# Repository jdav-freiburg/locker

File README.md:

# Fjaelllada - RFID controlled lockers 

> The following documentation is still work in progress, 
> for example documentation for the `depot_bay` flavor is very incomplete.

RFID accesible hardware lockers.  
Fjaelllada comes in two flavours:
* `depot_bay`: The big locker station used downstairs
* `seil_locker`: Single lock locker used upstairs for the ropes.

## Hardware

### depot_bay
_todo_

### seil_locker
See the [depot-oben-eda](depot-oben-eda) folder for kicad Drawings
Open the project file with [KiCad](https://www.kicad.org/) (used version is 8) to view the schematic and board design
for the small transistor board for opening the solenoid.

The pinout for the Raspberry Pi is as follows (BCM numbering!):

Pull up `SWITCH` to turn on the solenoid, don't hold too long because it tends to overheat quite fast. (<= 500 ms)
`CHECK` is high-z when the locker is open and GND when it is closed. To prevent floating state
pull up the GPIO pin to which `CHECK` is connected.

| Board Pin | RaspberryPi Pin |
| :-------- | :-------------- |
| SWITCH    | GPIO21          |
| CHECK     | GPIO20          |
| GND       | GND             |

For pinout info see [pinout.xyz/](https://pinout.xyz/)

## Software
See the [Software Docs](software/README.md) for details.

## Deployment

There is seperate [guide](Deployment.md) for how to deploy the software from scratch.

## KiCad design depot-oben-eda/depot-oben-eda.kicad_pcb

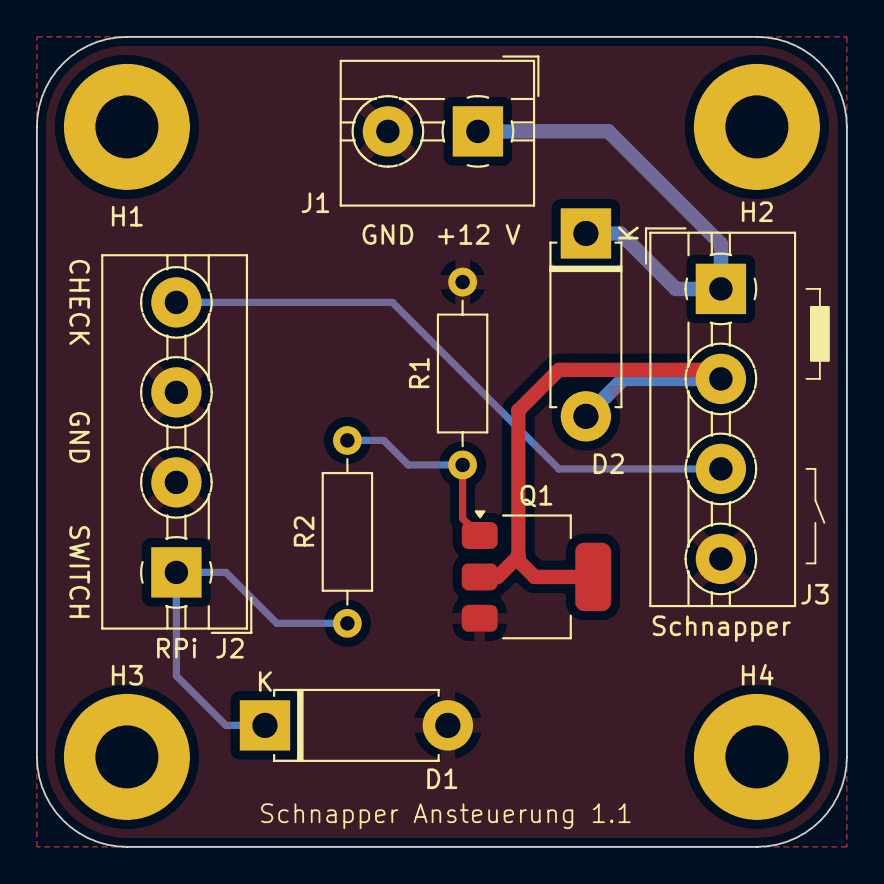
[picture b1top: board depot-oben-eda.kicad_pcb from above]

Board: 2 copper layers, 45.0 x 45.0 mm, 12 parts (0 on the bottom side), 6 nets.

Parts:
D1: 3V3; D_5W_P10.16mm_Horizontal
D2: 1N4007; D_5W_P10.16mm_Horizontal
H1: H1; MountingHole_3.5mm_Pad
H2: H2; MountingHole_3.5mm_Pad
H3: H3; MountingHole_3.5mm_Pad
H4: H4; MountingHole_3.5mm_Pad
J1: SUPPLY; TerminalBlock_MaiXu_MX126-5.0-02P_1x02_P5.00mm
J2: RPi; TerminalBlock_MaiXu_MX126-5.0-04P_1x04_P5.00mm
J3: Schnapper; TerminalBlock_MaiXu_MX126-5.0-04P_1x04_P5.00mm
Q1: BSP76; SOT-223-3_TabPin2
R1: 10k; R_Axial_DIN0207_L6.3mm_D2.5mm_P10.16mm_Horizontal
R2: 100; R_Axial_DIN0207_L6.3mm_D2.5mm_P10.16mm_Horizontal

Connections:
+12V: D2.1 (K), J1.1, J3.1
/BSP_DRAIN: D2.2 (A), J3.2, Q1.2 (D)
/CHECK: J2.4, J3.3
/SWITCH: D1.1 (K), J2.1, R2.1
GND: D1.2 (A), J1.2, J2.2, J2.3, J3.4, Q1.3 (S), R1.2
unnamed: Q1.1 (G), R1.1, R2.2

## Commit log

2024-02-10 Implement working administration, registration and card auth
2024-05-01 Add xsession
2024-12-07 feat: SMBus controller for bay
2024-12-07 Refactor repository
2024-12-07 Refactoring
2024-12-07 Refactor DB, remove timestamps
2024-12-07 Add sync of database
2024-12-07 Working locker
2024-12-07 Fix screen resolution env
2024-12-07 Make bus pin configurable
2024-12-07 Change pulldown to pullup
2024-12-07 Fix nonexisting db
2024-12-07 Fix typing
2024-12-08 checkin schematic and PCB layout for the solenoid control circuit
2024-12-08 create poetry project structure
2024-12-09 move files to more clearly named folder
2024-12-09 add cli links to scripts
2024-12-09 refactor readme files
2024-12-09 remove lock files from git
2024-12-09 Add all authors
2024-12-09 Add justfile and extended README
2024-12-09 Fix reader emulation Fix text database last changed Add more readme setup instructions Fixes #4
2024-12-12 Add Docs for deployment and db structure
2024-12-12 * Pin some packages to match the versions of the debian package * Add swig info to Readme
2024-12-12 rename commands to match docs and code
2024-12-12 Use python-dotenv package to enable loading env vars from an .env file
2025-01-17 Finish docs for setting up fjaelllada
2025-01-17 * Split documentation across multiple files. * Add more documentation
2025-01-17 Bump fjaelllada version
2025-01-26 hotfix: adapt pin numbers to current pinout
2025-01-26 * Change footprint of BSP76 to have D on Pin 4 * Move silkscreen of supply terminal down * increase GND spoke width
